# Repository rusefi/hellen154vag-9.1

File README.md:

# hellen154vag-9.1

[Board Wiki](https://github.com/rusefi/rusefi/wiki/Hellen-Vag-GDI)

https://github.com/andreika-git/hellen-one/

https://github.com/rusefi/rusefi

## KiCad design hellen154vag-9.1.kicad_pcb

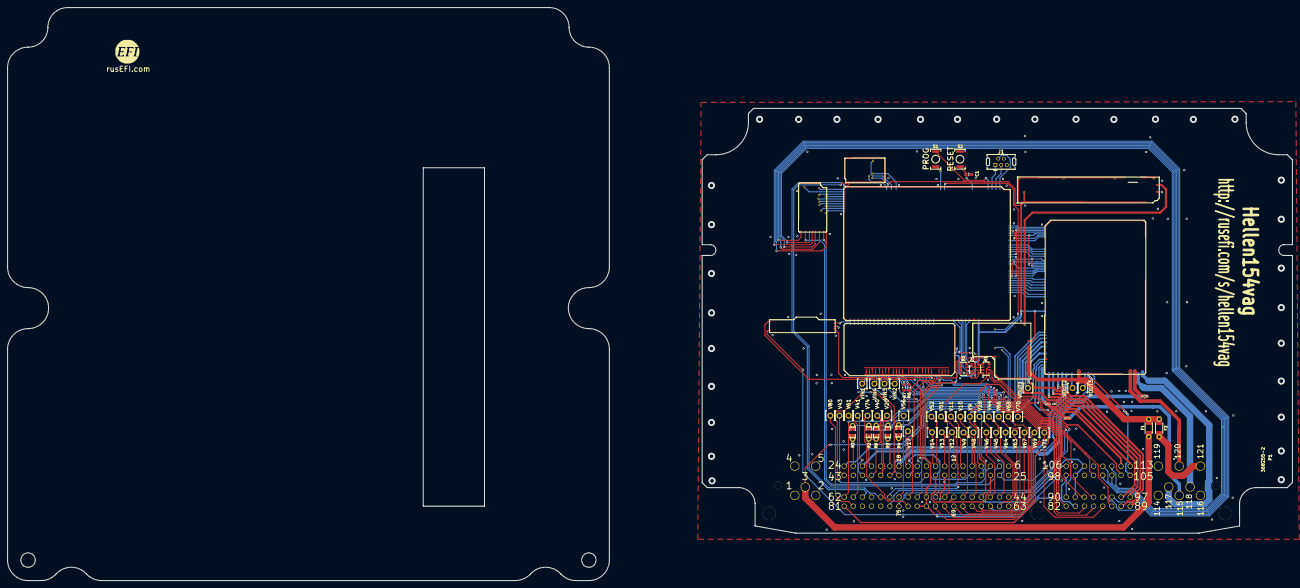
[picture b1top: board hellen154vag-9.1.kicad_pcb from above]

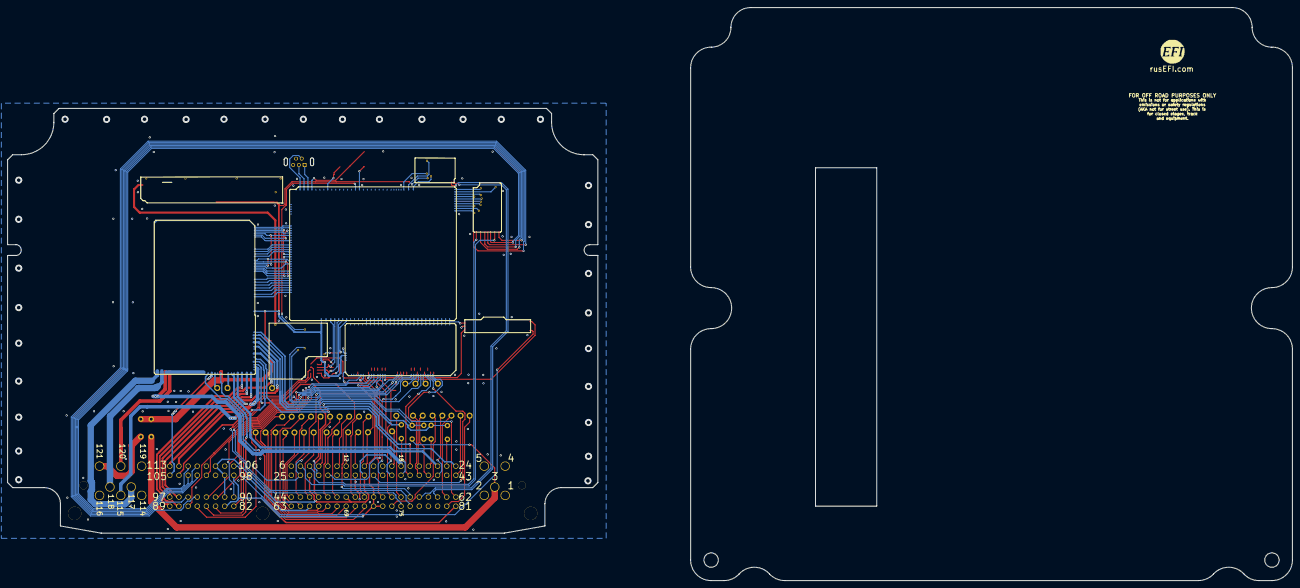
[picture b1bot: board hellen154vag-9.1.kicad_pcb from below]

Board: 2 copper layers, 164.0 x 118.0 mm, 66 parts (2 on the bottom side), 173 nets.

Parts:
C1: Cap; C0603
D1: D_TVS_Array_4; SOT23-6
F1, F2: Fuse-Pad-Pad; PAD-1206-PAD
G?: LOGO
G?#2: Disclaimer; Off_Road_Disclaimer
G?#3: LOGO
J1: USB_B_Mini; USB-MINI-B-VERTICAL
M1: Module-can-0.1; can
M2: Module-power5-0.1; power5
M3: Module-mcu-0.1; mcu
M4: Module-input-0.1; input
M5: Module-knock-0.1; knock
M6: Module-output-0.1; output
M7: Module-ign8-0.1; ign8
M8: Module-power12-0.1; power12
P1: 368255-2
R1, R5: Res_Array_4; R0603-4
R2, R3, R4, R8, R9: Jumper-Pad-Pad; PAD-0805-PAD
R6, R7: Res; R0603
S1, S2: Button_SPST; SMD-2_2.9x3.9x1.7
V9, V10, V11, V12, V13, V14, V17, V20, V28, V40, V41, V43, V44, V45, V46, V48, V49, V51, V52, V56, V61, V63, V64, V66, V67, V68, V69, V70, V71, V74, V80: Pad; PAD-TH
VIN1, VIN2, VIN3, VIN4: Pad; PAD-TH
VOUT1, VOUT2, VOUT3: Pad; PAD-TH

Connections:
+3V3: M3.N16 (V33), S1.2
+5V: D1.5, M1.V1 (V5), M2.V2 (V5), M3.S1 (V5), M4.E2 (V5), M6.W14 (V5), M8.E1 (V5)
+12V: M2.V1 (V12), M8.V1 (V12)
/A1: M3.S30 (IN_O2S2), M4.N4 (O2S2)
/A2: M3.S22 (IN_MAP3), M4.N12 (MAP3)
/A3: M3.S26 (IN_AUX3), M4.N8 (AUX3)
/A4: M3.S23 (IN_RES3), M4.N11 (RES3)
/AFR: M3.S16 (IN_O2S), M4.N18 (O2S)
/BOOT0: M3.N28 (BOOT0), S1.1
/CAM1: M3.S15 (IN_CAM), M4.N19 (CAM)
/CAM2: M3.S27 (IN_AUX4), M4.N7 (AUX4)
/CANH: M1.S2 (CANH), P1.60
/CANL: M1.S1 (CANL), P1.58
/CAN_RX: M1.V6 (CAN_RX), M3.N2 (CAN_RX)
/CAN_TX: M1.V5 (CAN_TX), M3.N3 (CAN_TX)
/CAN_VIO: M1.V2 (CAN_VIO), M3.N1 (CAN_VIO)
/CE: M3.E22 (OUT_IO11), M6.W25 (LOW4_DIODE)
/CLT: M3.S18 (IN_CLT), M4.N16 (CLT)
/COIL_A1: M3.E14 (OUT_PWM1), M6.W33 (SOLENOID_A1)
/COIL_A2: M3.E15 (OUT_PWM2), M6.W32 (SOLENOID_A2)
/CRANK: M3.S13 (IN_CRANK), M4.N21 (CRANK)
/D1: D1.4, M3.S3 (IN_D1), R1.1, R5.8
/D2: D1.6, M3.S4 (IN_D2), R1.2, R5.7
/D3: D1.1, M3.S5 (IN_D3), R1.3, R5.6
/D4: D1.3, M3.S6 (IN_D4), R1.4, R5.5
/FUEL_CONSUM: M3.E19 (OUT_PWM6), M6.W22 (PP2)
/IAT: M3.S19 (IN_IAT), M4.N15 (IAT)
/IDLE: M3.E18 (OUT_PWM5), M6.W38 (LOW1_DUAL)
/IGN1: M3.W1 (OUT_IGN1), M7.V8 (IGN1)
/IGN2: M3.W2 (OUT_IGN2), M7.V7 (IGN2)
/IGN3: M3.W3 (OUT_IGN3), M7.V6 (IGN3)
/IGN4: M3.W4 (OUT_IGN4), M7.V5 (IGN4)
/IGN5: M3.W5 (OUT_IGN5), M7.V4 (IGN5)
/IGN6: M3.W6 (OUT_IGN6), M7.V3 (IGN6)
/IGN7: M3.W7 (OUT_IGN7), M7.V2 (IGN7)
/IGN8: M3.W8 (OUT_IGN8), M7.V1 (IGN8)
/IGN_V5: M3.W9 (IGN_V5), M7.V9 (VCC)
/IGN_V33: M3.W10 (IGN_V33), M7.V10 (V33)
/INJ1: M3.E25 (OUT_INJ1), M6.W24 (INJ1)
/INJ2: M3.E26 (OUT_INJ2), M6.W23 (INJ2)
/INJ3: M3.E29 (OUT_INJ3), M6.W20 (INJ3)
/INJ4: M3.E30 (OUT_INJ4), M6.W19 (INJ4)
/INJ5: M3.E31 (OUT_INJ5), M6.W18 (INJ5)
/INJ6: M3.E32 (OUT_INJ6), M6.W17 (INJ6)
/INJ7: M3.E33 (OUT_INJ7), M6.W16 (INJ7)
/INJ8: M3.E34 (OUT_INJ8), M6.W15 (INJ8)
/IN_A1: M4.S25 (IN_O2S2), VIN1.1
/IN_A2: M4.S19 (IN_MAP3), VIN2.1
/IN_A3: M4.S20 (IN_AUX3), VIN3.1
/IN_A4: M4.S22 (IN_RES3), VIN4.1
/IN_AFR: M4.S9 (IN_O2S), P1.14, V14.1
/IN_CAM1: M4.S5 (IN_CAM), P1.86
/IN_CAM2: M4.S21 (IN_AUX4), P1.87
/IN_CLT: M4.S15 (IN_CLT), P1.93, R6.1
/IN_CRANK: M4.S8 (IN_CRANK), P1.82
/IN_D1: P1.55, R1.8
/IN_D2: P1.57, R1.7
/IN_D3: P1.75, R1.6
/IN_D4: P1.76, R1.5
/IN_IAT: M4.S16 (IN_IAT), P1.26, P1.85, R7.1
/IN_KNOCK1: M4.S7 (IN_KNOCK), M5.E3 (OUT_KNOCK)
/IN_KNOCK1_RAW: M5.W1 (IN_KNOCK), P1.106
/IN_MAF: M4.S11 (IN_MAP1), P1.29
/IN_MAP2: M4.S12 (IN_MAP2), P1.101
/IN_PPS1: M4.S24 (IN_PPS), P1.34
/IN_PPS2: M4.S18 (IN_AUX2), P1.35
/IN_RES1: M4.S23 (IN_RES1), P1.38
/IN_RES2: M4.S26 (IN_RES2), P1.39
/IN_TPS1: M4.S10 (IN_TPS), P1.92
/IN_TPS2: M4.S17 (IN_AUX1), P1.84
/IN_VIGN: M8.V3 (IN_VIGN), R8.2, R9.2
/IN_VSS: M4.S6 (IN_VSS), P1.54
/KNOCK1: M3.S12 (IN_KNOCK), M4.N22 (KNOCK)
/MAF: M3.S20 (IN_MAP1), M4.N14 (MAP1)
/MAIN: M3.E6 (OUT_IO1), M6.W40 (LOW3_MAIN)
/MAP2: M3.S21 (IN_MAP2), M4.N13 (MAP2)
/NRESET: C1.2, M3.N24 (nReset), S2.1
/OUT1: M3.E7 (OUT_IO2), M6.W39 (LOW5_HIGH1)
/OUT2: M3.E9 (OUT_IO4), M6.W37 (LOW6_HIGH2)
/OUT3: M3.E28 (OUT_PWM8), M6.W21 (LOW8)
/OUT_CE: M6.W3 (OUT_LOW4_DIODE), P1.47
/OUT_COIL_A1: M6.S1 (OUT_SOLENOID_A1), P1.117
/OUT_COIL_A2: M6.S2 (OUT_SOLENOID_A2), P1.118
/OUT_FUEL_CONSUM: M6.S6 (OUT_PP2), P1.81
/OUT_IDLE: M6.S7 (OUT_LOW1_DUAL), P1.105
/OUT_IGN1: M7.S8 (OUT_IGN1), P1.102
/OUT_IGN2: M7.S7 (OUT_IGN2), P1.7
/OUT_IGN3: M7.S6 (OUT_IGN3), P1.111
/OUT_IGN4: M7.S5 (OUT_IGN4), P1.94
/OUT_IGN5: M7.S4 (OUT_IGN5), P1.103
/OUT_IGN6: M7.S3 (OUT_IGN6), P1.110
/OUT_IGN7: M7.S2 (OUT_IGN7), P1.8
/OUT_IGN8: M7.S1 (OUT_IGN8), P1.95
/OUT_INJ1: M6.S18 (OUT_INJ1), P1.96
/OUT_INJ2: M6.S16 (OUT_INJ2), P1.89
/OUT_INJ3: M6.S17 (OUT_INJ3), P1.97
/OUT_INJ4: M6.W7 (OUT_INJ4), P1.88
/OUT_INJ5: M6.W10 (OUT_INJ5), P1.113
/OUT_INJ6: M6.S15 (OUT_INJ6), P1.112
/OUT_INJ7: M6.W12 (OUT_INJ7), P1.19
/OUT_INJ8: M6.W11 (OUT_INJ8), P1.24
/OUT_MAIN: M6.W13 (OUT_LOW3_MAIN), R2.2, R3.2
/OUT_PUMP: M6.S10 (OUT_LOW10), P1.65
/OUT_TACH: M6.W6 (OUT_PP1), R4.2
/OUT_VVT1_1: M6.S13 (OUT_LOW11), M6.S14 (OUT_LOW7), P1.22
/OUT_VVT1_2: M6.W1 (OUT_LOW12), M6.W2 (OUT_LOW9), P1.115
/OUT_VVT2_B1: M6.S4 (OUT_SOLENOID_B1), P1.18
/OUT_VVT2_B2: M6.S5 (OUT_SOLENOID_B2), P1.120
/OUT_WASTEGATE: M6.W4 (OUT_LOW2_DUAL), P1.104
/PPS1: M3.S29 (IN_PPS), M4.N5 (PPS)
/PPS2: M3.S25 (IN_AUX2), M4.N9 (AUX2)
/PUMP: M3.E8 (OUT_IO3), M6.W35 (LOW10)
/RES1: M3.S28 (IN_RES1), M4.N6 (RES1)
/RES2: M3.S31 (IN_RES2), M4.N3 (RES2)
/TACH: M3.E27 (OUT_PWM7), M6.W28 (PP1)
/TPS1: M3.S17 (IN_TPS), M4.N17 (TPS)
/TPS2: M3.S24 (IN_AUX1), M4.N10 (AUX1)
/USBM: J1.2 (D-), M3.N31 (USB1M)
/USBP: J1.3 (D+), M3.N30 (USB1P)
/V12_PERM: M8.V4 (V12_PERM), P1.62
/VBAT: M3.N17 (VBAT), M8.V2 (VBAT)
/VBUS: J1.1 (VBUS), M3.N29 (VBUS)
/VIGN: M3.S7 (VIGN), M8.V5 (VIGN)
/VREF1: M4.S14 (VREF1), P1.90
/VREF2: M4.S13 (VREF2), M5.W2 (VREF)
/VSS: M3.S14 (IN_VSS), M4.N20 (VSS)
/VVT1_1: M3.E10 (OUT_IO5), M6.W27 (LOW7), M6.W36 (LOW11)
/VVT1_2: M3.E21 (OUT_IO10), M6.W26 (LOW9), M6.W29 (LOW12)
/VVT2_B1: M3.E16 (OUT_PWM3), M6.W31 (SOLENOID_B1)
/VVT2_B2: M3.E17 (OUT_PWM4), M6.W30 (SOLENOID_B2)
/WASTEGATE: M3.E12 (OUT_IO7), M6.W34 (LOW2_DUAL)
GND: C1.1, D1.2, J1.5 (GND), M1.E1 (GND), M2.G (GND), M3.S2 (GND), M4.E1 (GND), M5.E2 (GND), M6.G (GND), M6.S3 (GND), M7.G (GND), M8.S1 (GND), P1.1, P1.2, P1.32, P1.59, R5.1, R5.2, R5.3, R5.4, S2.2
GNDA: M3.S32 (GNDA), M4.J2 (PULL_GNDA), M4.J3 (PULL_RES2), M4.J4 (PULL_O2S2), M4.J6 (PULL_RES1), M4.J8 (PULL_AUX3), M4.J11 (PULL_RES3), M4.J12 (PULL_MAP3), M4.J13 (PULL_MAP2), M4.J14 (PULL_MAP1), M4.J22 (PULL_KNOCK), M4.J24 (PULL_SENS3), M4.N2 (GNDA), P1.27, P1.33, P1.36, P1.50, P1.91, P1.99, P1.108, R6.2, R7.2
unnamed: F1.1, P1.3, R9.1
unnamed: F2.1, P1.121
unnamed: M6.S8 (OUT_LOW8), VOUT3.1
unnamed: M6.S12 (OUT_LOW6_PULLUP), VOUT2.1
unnamed: M6.W9 (OUT_LOW5_PULLUP), VOUT1.1
unnamed: P1.9, V9.1
unnamed: P1.10, V10.1
unnamed: P1.11, V11.1
unnamed: P1.12, V12.1
unnamed: P1.13, V13.1
unnamed: P1.17, V17.1
unnamed: P1.20, V20.1
unnamed: P1.21, R2.1, R8.1
unnamed: P1.23, R3.1
unnamed: P1.28, V28.1
unnamed: P1.37, R4.1
unnamed: P1.40, V40.1
unnamed: P1.41, V41.1
unnamed: P1.43, V43.1
unnamed: P1.44, V44.1
unnamed: P1.45, V45.1
unnamed: P1.46, V46.1
unnamed: P1.48, V48.1
unnamed: P1.49, V49.1
unnamed: P1.51, V51.1
unnamed: P1.52, V52.1
unnamed: P1.56, V56.1
unnamed: P1.61, V61.1
unnamed: P1.63, V63.1
unnamed: P1.64, V64.1
unnamed: P1.66, V66.1
unnamed: P1.67, V67.1
unnamed: P1.68, V68.1
unnamed: P1.69, V69.1
unnamed: P1.70, V70.1
unnamed: P1.71, V71.1
unnamed: P1.74, V74.1
unnamed: P1.80, V80.1
V5A: M3.S33 (V5A), M4.E5 (V5A), M4.J1 (PULL_V5A), M4.J5 (PULL_PPS), M4.J7 (PULL_AUX4), M4.J9 (PULL_AUX2), M4.J10 (PULL_AUX1), M4.J17 (PULL_CAM), M4.J18 (PULL_VSS), M4.J19 (PULL_TPS), M4.J20 (PULL_O2S), M4.J21 (PULL_CRANK), M4.N1 (V5A), M5.E1 (V5A), P1.53, P1.72, P1.73, P1.83, P1.98
V12_RAW: F1.2, F2.2, M6.S11 (V12_RAW), M8.E2 (V12_RAW)

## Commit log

2021-03-06 we have board outline, we have useful submodules
2021-03-10 Removed some template files.
2021-03-10 Initial copy from hellen121vag Basic starting point has been created.
2021-03-11 Added 33816 sub schematic changed 121 connector to 154 connector Initial draft schematic. Many nets are not properly connected.
2021-03-11 Added injector net names to the sheet labels.
2021-03-11 useful file
2021-03-31 Initial attempt at connecting connector to circuits. Currently many errors.
2021-04-11 fresh h1
2021-05-09 Connected several more nets. Still missing ETB, and VR. It still needs several nets to be connected.
2021-05-09 Updated KC nightly builds version
2021-05-16 Updated to most recent VAG121 layout, which adds ETB and VR circuits.
2021-05-16 MISC net names were connected, like ETB and VR nets are now connected.
2021-05-16 This time I really did connect the VR net.
2021-05-16 Connected IN_RES1 and IN_RES2 as fuel pump analog inputs.
2021-05-23 DI IO are mostly connected, nets with titles like this need to be connected to STM32 TBD_### https://github.com/rusefi/hellen154vag-9.1/issues/4
2021-05-23 Need to resolved TBD_###_or_### Two different potential pin outs found at the below, top of page and bottom of page have different pin-outs. https://github.com/rusefi/rusefi/wiki/MC33816-PT2001-dev-b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
    https://github.com/rusefi/hellen154vag-9.1/issues/4
2021-05-23 JH does not see hot all times for 154, like 121 had. I made a best guess and added 0R W jumpers. 154 schematic found here https://github.com/rusefi/rusefi/wiki/VolkswagenPassatB6 121 schematic found 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
    https://github.com/rusefi/hellen154vag-9.1/issues/5
2021-05-23 More nets connected, 2 are unresolved, TBD_PD4_or_PA15 and TBD_PD3_or_PC13. These IO are not connected to the STM32. Need to know what to connect them to. https://github.com/rusefi/hellen154vag-9.1/i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
2021-05-25 draft PDF
2021-05-30 Connected DI IO to E20 and E24. Deleted unused schematic pieces, should be ready for PCB layout. https://github.com/rusefi/hellen154vag-9.1/issues/4
2021-05-31 Changed to pull down resistor, removed series resistor. https://github.com/rusefi/hellen154vag-9.1/issues/6
